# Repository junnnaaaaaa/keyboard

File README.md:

Current version: Testicular Corne v4

Changes from Testicular Corne v3:
- rid of the immature diode cluster
- direction arrows on each diode
- flavour text
- ground plane

Todo:
- Make some firmware !!
- The case
- The plate

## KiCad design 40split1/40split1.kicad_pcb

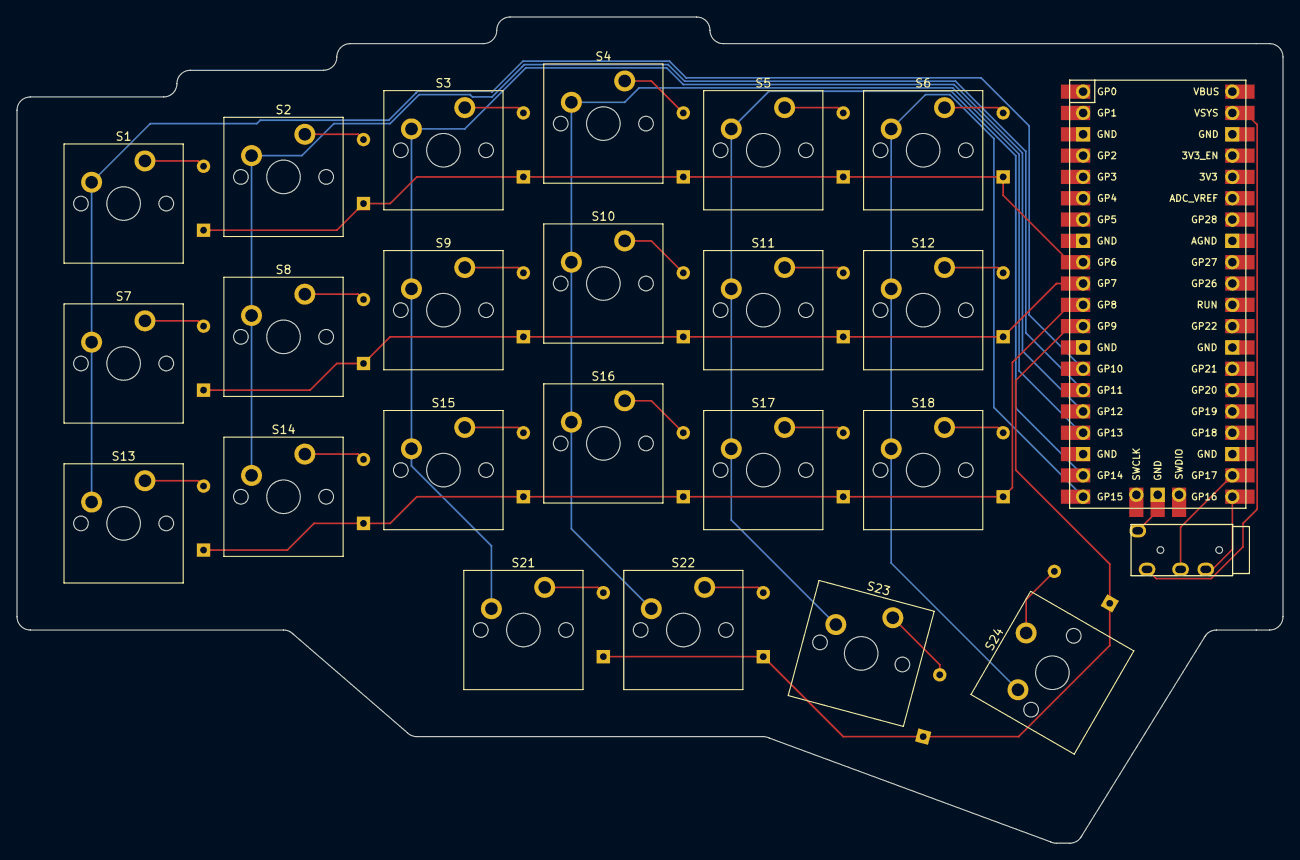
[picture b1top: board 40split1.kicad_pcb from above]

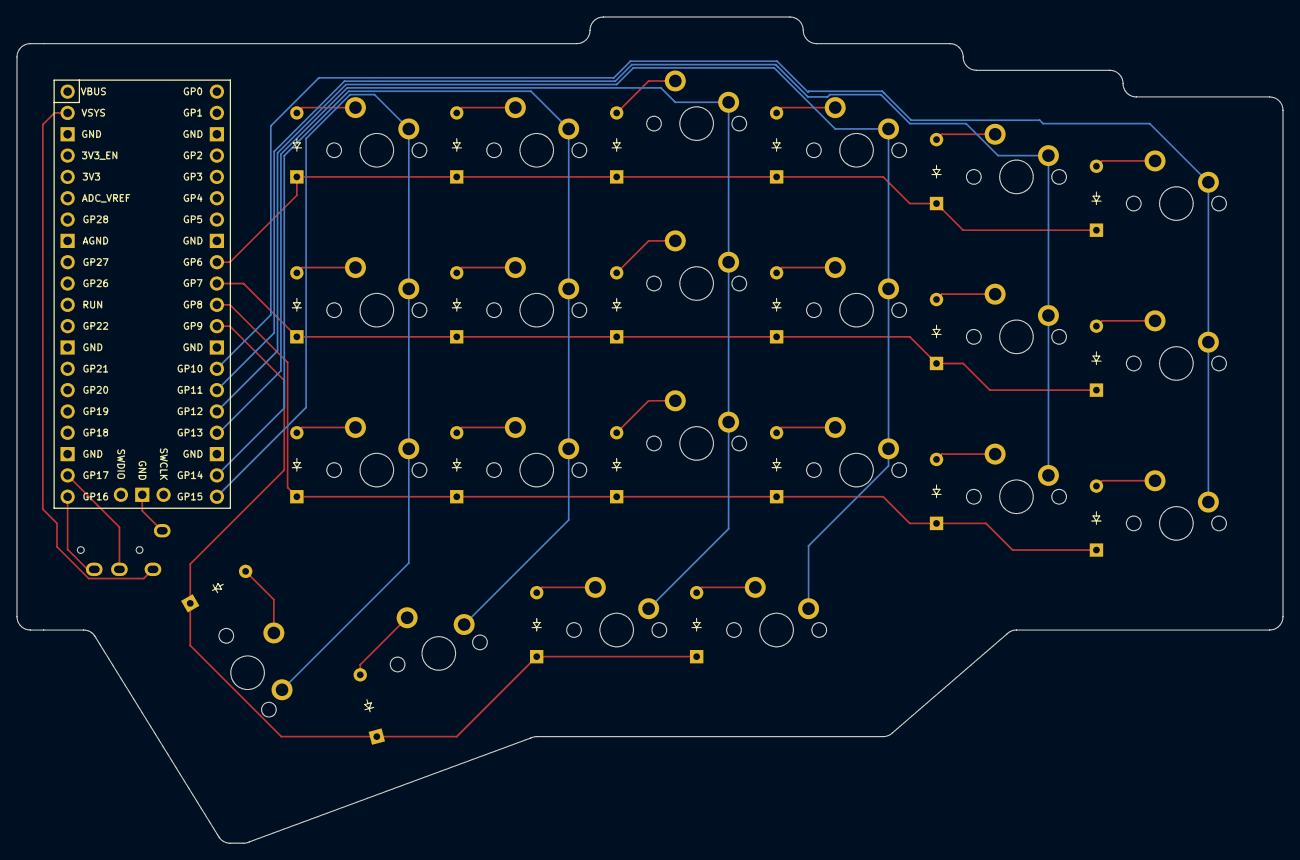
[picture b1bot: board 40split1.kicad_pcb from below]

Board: 2 copper layers, 150.8 x 98.4 mm, 46 parts (22 on the bottom side), 36 nets.

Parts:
D1, D2, D3, D4, D5, D6, D7, D8, D9, D10, D11, D12, D13, D14, D15, D16, D17, D18, D21, D22, D23, D24: Diode; Diode_DO-35
S1, S2, S3, S4, S5, S6, S7, S8, S9, S10, S11, S12, S13, S14, S15, S16, S17, S18, S21, S22, S23: Keyswitch; MX_PCB_1.00u
S24: Keyswitch; MX_PCB_1.50u
U1: Raspberry_Pi_Pico
U2: TRRS; TRRS_PJ-320A

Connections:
Col 0: S1.1, S7.1, S13.1, U1.14 (GPIO10)
Col 1: S2.1, S8.1, S14.1, U1.15 (GPIO11)
Col 2: S3.1, S9.1, S15.1, S21.1, U1.16 (GPIO12)
Col 3: S4.1, S10.1, S16.1, S22.1, U1.17 (GPIO13)
Col 4: S5.1, S11.1, S17.1, S23.1, U1.19 (GPIO14)
Col 5: S6.1, S12.1, S18.1, S24.1, U1.20 (GPIO15)
unnamed: D1.2 (A), S1.2
unnamed: D2.2 (A), S2.2
unnamed: D3.2 (A), S3.2
unnamed: D4.2 (A), S4.2
unnamed: D5.2 (A), S5.2
unnamed: D6.2 (A), S6.2
unnamed: D7.2 (A), S7.2
unnamed: D8.2 (A), S8.2
unnamed: D9.2 (A), S9.2
unnamed: D10.2 (A), S10.2
unnamed: D11.2 (A), S11.2
unnamed: D12.2 (A), S12.2
unnamed: D13.2 (A), S13.2
unnamed: D14.2 (A), S14.2
unnamed: D15.2 (A), S15.2
unnamed: D16.2 (A), S16.2
unnamed: D17.2 (A), S17.2
unnamed: D18.2 (A), S18.2
unnamed: D21.2 (A), S21.2
unnamed: D22.2 (A), S22.2
unnamed: D23.2 (A), S23.2
unnamed: D24.2 (A), S24.2
Row 0: D1.1 (K), D2.1 (K), D3.1 (K), D4.1 (K), D5.1 (K), D6.1 (K), U1.9 (GPIO6)
Row 1: D7.1 (K), D8.1 (K), D9.1 (K), D10.1 (K), D11.1 (K), D12.1 (K), U1.10 (GPIO7)
Row 2: D13.1 (K), D14.1 (K), D15.1 (K), D16.1 (K), D17.1 (K), D18.1 (K), U1.11 (GPIO8)
Row 3: D21.1 (K), D22.1 (K), D23.1 (K), D24.1 (K), U1.12 (GPIO9)
Tip: U1.39 (VSYS), U2.2 (TIP)
r1: U1.22 (GPIO17), U2.3 (RING1)
r2: U1.21 (GPIO16), U2.4 (RING2)
sleeve: U1.42 (GND), U2.1 (SLEEVE)

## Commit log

2025-01-09 sorted out trrs
2025-01-09 positioned all diodes and keys, just need to do routing
2025-01-09 adjusted pico position
2025-01-09 adjusted schematics a little, finished all routing
2025-01-09 did the pcb cutout, flipped all the diodes
2025-03-13 Initial commit, complete rework of the keyboard from the ground up // UNFINISHED
2025-03-13 more work on the keyboard, added readme and a pic of the layout (use cascade btw)
2025-03-13 format readme
2025-03-13 added a pin assignment plan
2025-03-13 Update pin_assignments
2025-03-13 Fixed a bunch of errors, added more plans
2025-03-13 edit readme
2025-03-15 new diode cluster
2025-03-15 keycaps
2025-03-15 make some changes to the pcb
2025-03-26 Keyboard V4: Rearrange diodes
2025-03-26 documentation changes
2025-03-26 qmk begins.. a battle awaits
